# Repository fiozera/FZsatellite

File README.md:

# FZsatellite
Um satélite PocketQube Open Hardware

Projeto desenvolvido em colaboração com:

- Jonathan Querubina <https://github.com/chr0nu5>
- Pedro Kaled <https://github.com/pedrokdc>
- Edson Pavoni

Licensed under CERN-OHL-S v2 or later

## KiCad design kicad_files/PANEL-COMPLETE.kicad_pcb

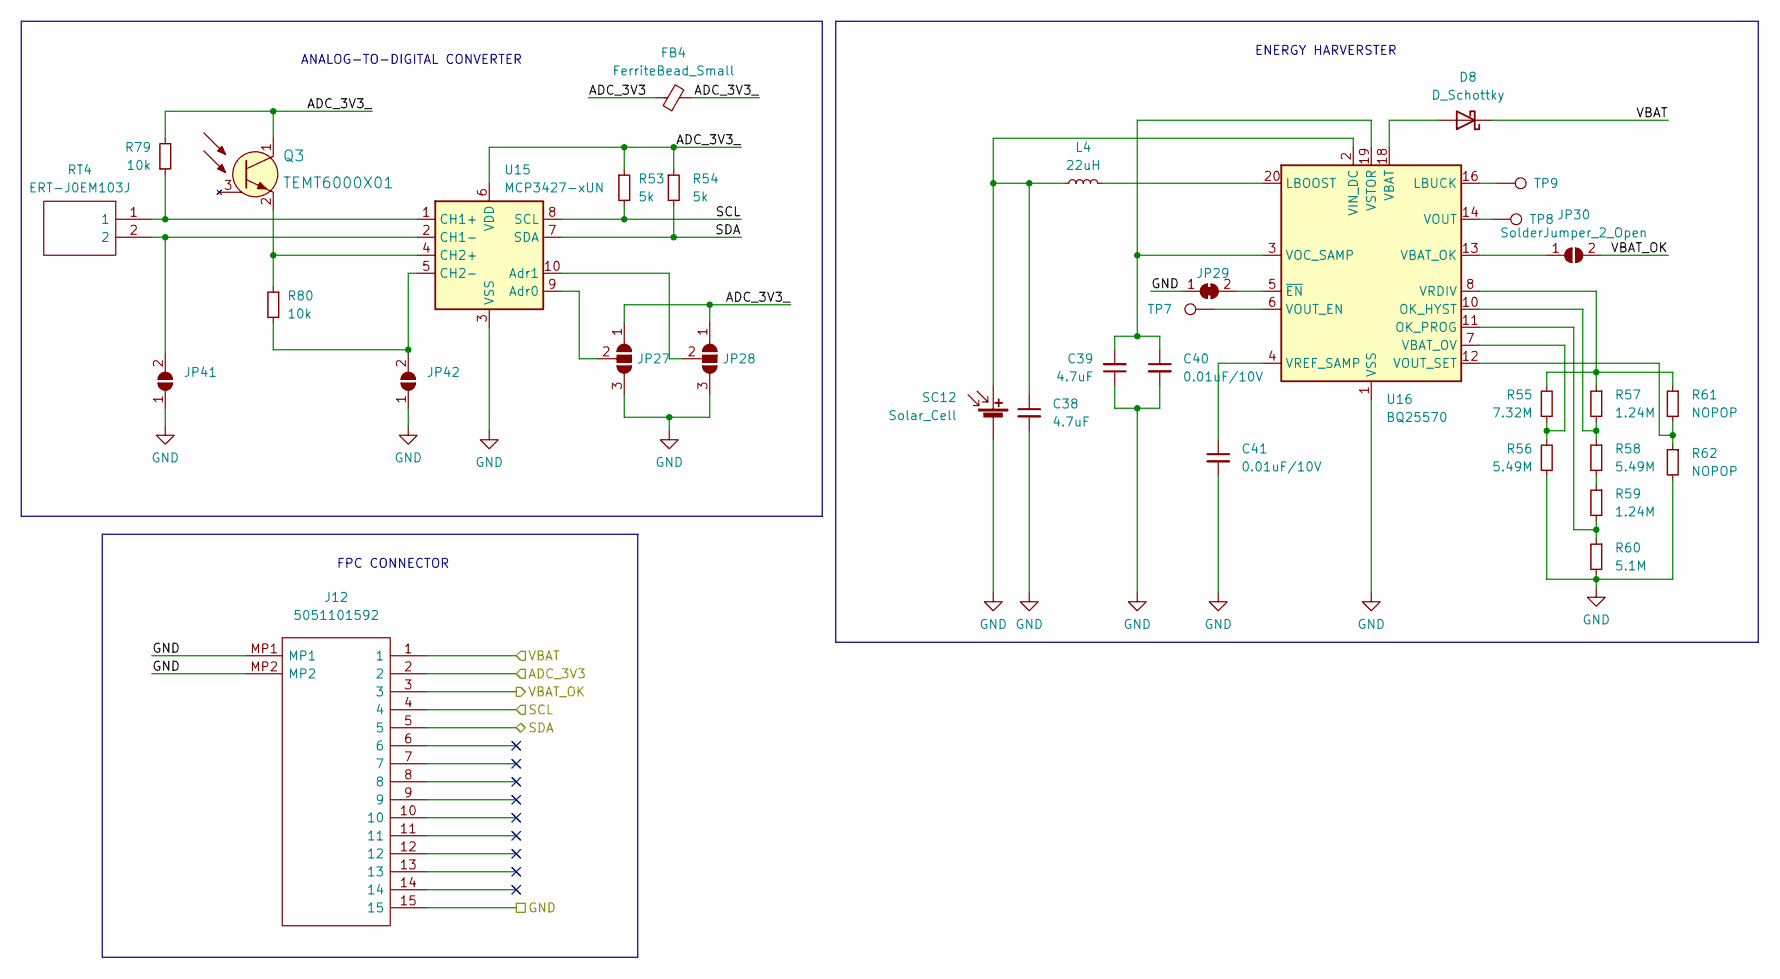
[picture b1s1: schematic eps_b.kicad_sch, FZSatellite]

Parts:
C38, C39: 4.7uF; C_0805_2012Metric
C40, C41: 0.01uF/10V; C_0402_1005Metric; Mouser Part 581-0402ZC103MAT2A
D8: D_Schottky; D_SOD-323
FB4: FerriteBead_Small; L_0603_1608Metric
J12: 5051101592; Manufacturer_Part_Number 5051101592
JP27, JP28: SolderJumper_3_Open; SolderJumper-3_P1.3mm_Open_RoundedPad1.0x1.5mm
JP29: SolderJumper_2_Bridged; SolderJumper-2_P1.3mm_Bridged_RoundedPad1.0x1.5mm
JP30, JP41, JP42: SolderJumper_2_Open; SolderJumper-2_P1.3mm_Open_RoundedPad1.0x1.5mm
L4: 22uH; LPS4018223MRC
Q3: TEMT6000X01; Phototransistor_SMD_4x2mm_TEMT6000X01; MPN TEMT6000X01; Digi-Key_PN 751-1055-1-ND
R53, R54: 5k; R_0402_1005Metric; Mouser Part 603-RC0402FR-075KL
R55: 7.32M; R_0402_1005Metric
R56, R58: 5.49M; R_0402_1005Metric
R57, R59: 1.24M; R_0402_1005Metric
R60: 5.1M; R_0402_1005Metric
R61, R62: NOPOP; R_0402_1005Metric
R79, R80: 10k; R_0603_1608Metric
RT4: ERT-J0EM103J; THRMC1005X55N; Mouser Part Number 667-ERT-J0EM103J
SC12: Solar_Cell; SM141K08LV
TP7, TP8, TP9: TestPoint; TestPoint_Pad_D1.0mm
U15: MCP3427-xUN; MSOP-10_3x3mm_P0.5mm
U16: BQ25570; QFN-20-1EP_3.5x3.5mm_P0.5mm_EP2x2mm

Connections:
/ADC_3V3: FB4.1, J12.2; also elsewhere on the board
/DEPNO: D8.1 (K), J12.1; also elsewhere on the board
/EPS B/ADC_3V3_: FB4.2, JP27.1 (A), JP28.1 (A), Q3.1 (C), R53.1, R54.1, R79.2, U15.6 (VDD)
/SCL1: J12.4, R53.2, U15.8 (SCL); also elsewhere on the board
/SDA1: J12.5, R54.2, U15.7 (SDA); also elsewhere on the board
/VBAT_OK: J12.3, JP30.2 (B); also elsewhere on the board
GND: C38.2, C39.1, C40.2, C41.2, J12.15, J12.MP1, J12.MP2, JP27.3 (B), JP28.3 (B), JP29.1 (A), JP41.1 (A), JP42.1 (A), R56.1, R60.2, R62.2, SC12.2 (-), U15.3 (VSS), U16.1 (VSS), U16.9 (VSS), U16.15 (VSS), U16.17 (VSS), U16.21 (VSS); also elsewhere on the board
unnamed: C38.1, L4.1, SC12.1 (+), U16.2 (VIN_DC)
unnamed: C39.2, C40.1, U16.3 (VOC_SAMP), U16.19 (VSTOR)
unnamed: C41.1, U16.4 (VREF_SAMP)
unnamed: D8.2 (A), U16.18 (VBAT)
unnamed: JP27.2 (C), U15.9 (Adr0)
unnamed: JP28.2 (C), U15.10 (Adr1)
unnamed: JP29.2 (B), U16.5 (~EN)
unnamed: JP30.1 (A), U16.13 (VBAT_OK)
unnamed: JP41.2 (B), RT4.2, U15.2 (CH1-)
unnamed: JP42.2 (B), R80.2, U15.5 (CH2-)
unnamed: L4.2, U16.20 (LBOOST)
unnamed: Q3.2 (E), R80.1, U15.4 (CH2+)
unnamed: R55.1, R56.2, U16.7 (VBAT_OV)
unnamed: R55.2, R57.1, R61.1, U16.8 (VRDIV)
unnamed: R57.2, R58.1, U16.10 (OK_HYST)
unnamed: R58.2, R59.1
unnamed: R59.2, R60.1, U16.11 (OK_PROG)
unnamed: R61.2, R62.1, U16.12 (VOUT_SET)
unnamed: R79.1, RT4.1, U15.1 (CH1+)
unnamed: TP7.1, U16.6 (VOUT_EN)
unnamed: TP8.1, U16.14 (VOUT)
unnamed: TP9.1, U16.16 (LBUCK)

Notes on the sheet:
FPC CONNECTOR
ANALOG-TO-DIGITAL CONVERTER
ENERGY HARVERSTER

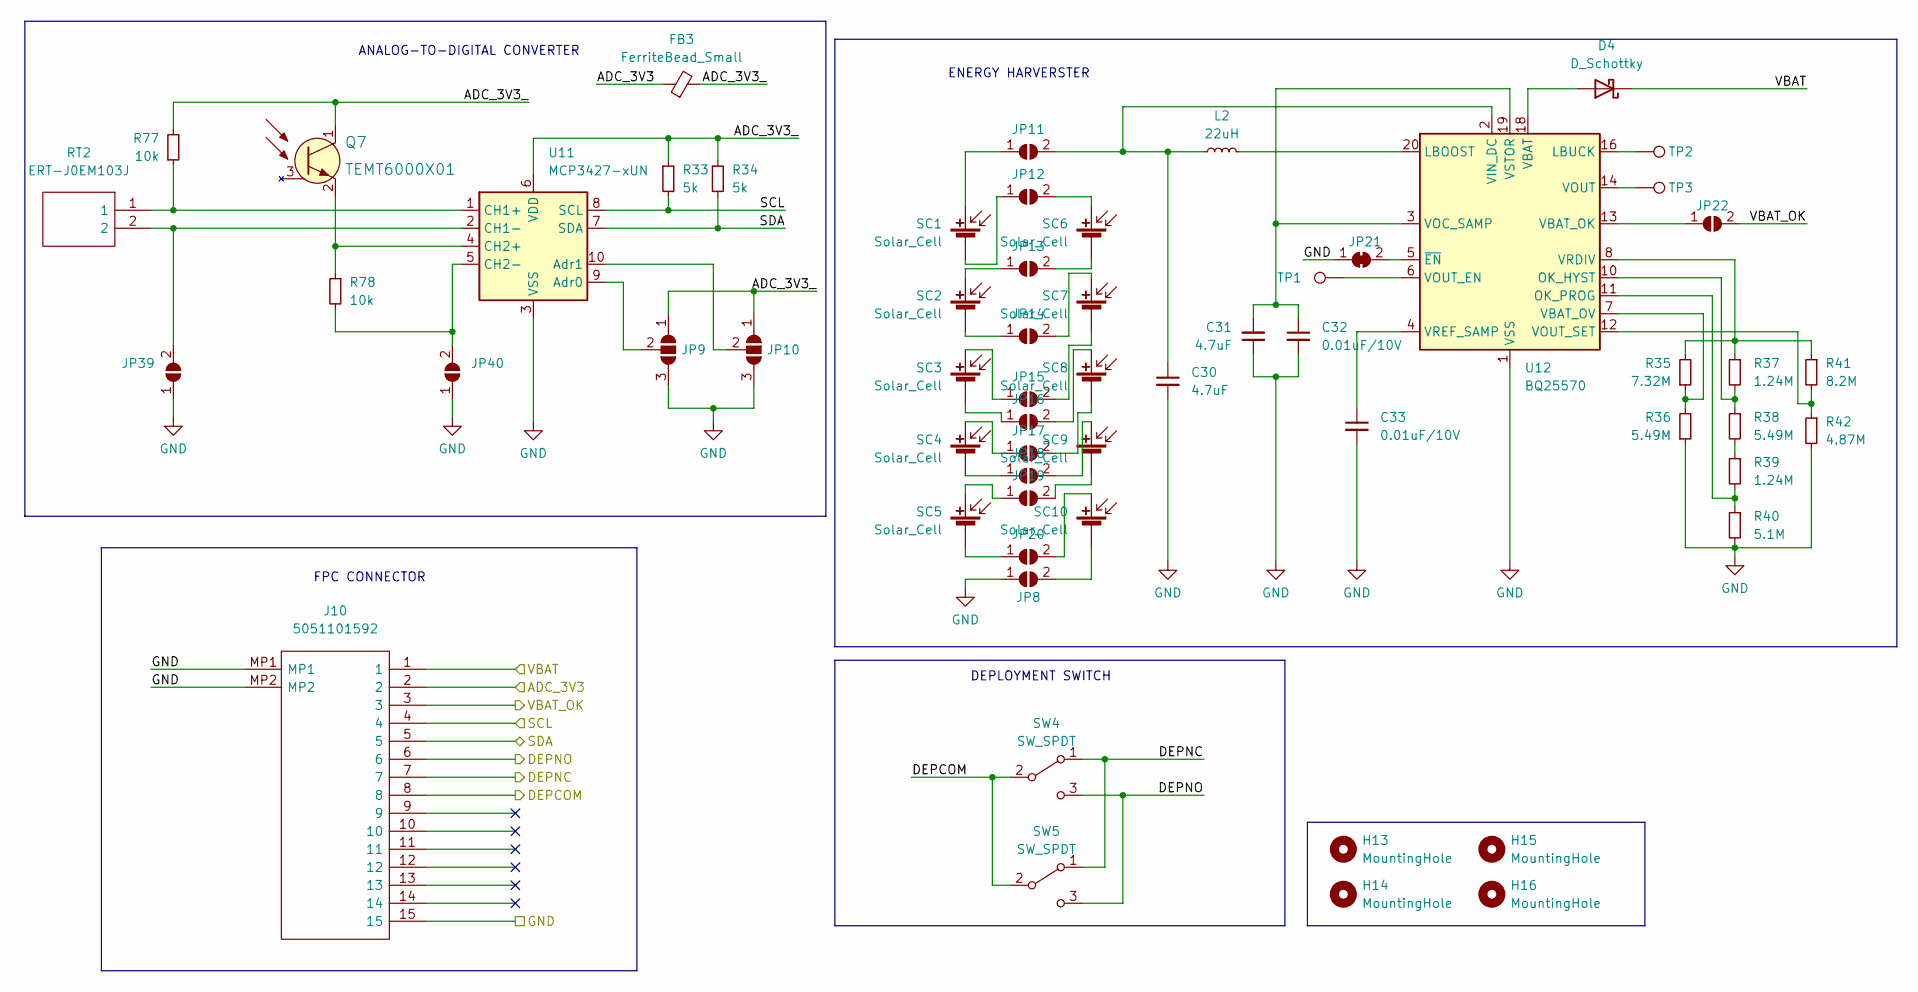
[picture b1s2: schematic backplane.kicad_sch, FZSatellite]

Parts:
C30, C31: 4.7uF; C_0805_2012Metric
C32, C33: 0.01uF/10V; C_0402_1005Metric; Mouser Part 581-0402ZC103MAT2A
D4: D_Schottky; D_SOD-323
FB3: FerriteBead_Small; L_0603_1608Metric
H13, H14, H15, H16: MountingHole; MountingHole_2.2mm_M2
J10: 5051101592; Manufacturer_Part_Number 5051101592
JP8, JP11, JP12, JP13, JP14, JP15, JP16, JP17, JP18, JP19, JP20, JP22, JP39, JP40: SolderJumper_2_Open; SolderJumper-2_P1.3mm_Open_RoundedPad1.0x1.5mm
JP9, JP10: SolderJumper_3_Open; SolderJumper-3_P1.3mm_Open_RoundedPad1.0x1.5mm
JP21: SolderJumper_2_Bridged; SolderJumper-2_P1.3mm_Bridged_RoundedPad1.0x1.5mm
L2: 22uH; LPS4018223MRC
Q7: TEMT6000X01; Phototransistor_SMD_4x2mm_TEMT6000X01; MPN TEMT6000X01; Digi-Key_PN 751-1055-1-ND
R33, R34: 5k; R_0402_1005Metric; Mouser Part 603-RC0402FR-075KL
R35: 7.32M; R_0402_1005Metric
R36, R38: 5.49M; R_0402_1005Metric
R37, R39: 1.24M; R_0402_1005Metric
R40: 5.1M; R_0402_1005Metric
R41: 8.2M; R_0402_1005Metric
R42: 4.87M; R_0402_1005Metric
R77, R78: 10k; R_0603_1608Metric
RT2: ERT-J0EM103J; THRMC1005X55N; Mouser Part Number 667-ERT-J0EM103J
SC1, SC2, SC3, SC4, SC5, SC6, SC7, SC8, SC9, SC10: Solar_Cell; KXOB25-12X1F-TR
SW4, SW5: SW_SPDT; D2F-L2-A1
TP1, TP2, TP3: TestPoint; TestPoint_Pad_D1.0mm
U11: MCP3427-xUN; MSOP-10_3x3mm_P0.5mm
U12: BQ25570; QFN-20-1EP_3.5x3.5mm_P0.5mm_EP2x2mm

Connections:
/ADC_3V3: FB3.1, J10.2; also elsewhere on the board
/BACK PLANE/ADC_3V3_: FB3.2, JP9.1 (A), JP10.1 (A), Q7.1 (C), R33.1, R34.1, R77.2, U11.6 (VDD)
/DEPCOM: J10.8, SW4.2 (B), SW5.2 (B); also elsewhere on the board
/DEPNC: J10.7, SW4.1 (A), SW5.1 (A); also elsewhere on the board
/DEPNO: D4.1 (K), J10.1, J10.6, SW4.3 (C), SW5.3 (C); also elsewhere on the board
/SCL1: J10.4, R33.2, U11.8 (SCL); also elsewhere on the board
/SDA1: J10.5, R34.2, U11.7 (SDA); also elsewhere on the board
/VBAT_OK: J10.3, JP22.2 (B); also elsewhere on the board
GND: C30.2, C31.1, C32.2, C33.2, J10.15, J10.MP1, J10.MP2, JP8.1 (A), JP9.3 (B), JP10.3 (B), JP21.1 (A), JP39.1 (A), JP40.1 (A), R36.1, R40.2, R42.2, U11.3 (VSS), U12.1 (VSS), U12.9 (VSS), U12.15 (VSS), U12.17 (VSS), U12.21 (VSS); also elsewhere on the board
unnamed: C30.1, JP11.2 (B), L2.1, U12.2 (VIN_DC)
unnamed: C31.2, C32.1, U12.3 (VOC_SAMP), U12.19 (VSTOR)
unnamed: C33.1, U12.4 (VREF_SAMP)
unnamed: D4.2 (A), U12.18 (VBAT)
unnamed: JP8.2 (B), SC10.2 (-)
unnamed: JP9.2 (C), U11.9 (Adr0)
unnamed: JP10.2 (C), U11.10 (Adr1)
unnamed: JP11.1 (A), SC1.1 (+)
unnamed: JP12.1 (A), SC1.2 (-)
unnamed: JP12.2 (B), SC6.1 (+)
unnamed: JP13.1 (A), SC2.1 (+)
unnamed: JP13.2 (B), SC6.2 (-)
unnamed: JP14.1 (A), SC2.2 (-)
unnamed: JP14.2 (B), SC7.1 (+)
unnamed: JP15.1 (A), SC3.1 (+)
unnamed: JP15.2 (B), SC7.2 (-)
unnamed: JP16.1 (A), SC3.2 (-)
unnamed: JP16.2 (B), SC8.1 (+)
unnamed: JP17.1 (A), SC4.1 (+)
unnamed: JP17.2 (B), SC8.2 (-)
unnamed: JP18.1 (A), SC4.2 (-)
unnamed: JP18.2 (B), SC9.1 (+)
unnamed: JP19.1 (A), SC5.1 (+)
unnamed: JP19.2 (B), SC9.2 (-)
unnamed: JP20.1 (A), SC5.2 (-)
unnamed: JP20.2 (B), SC10.1 (+)
unnamed: JP21.2 (B), U12.5 (~EN)
unnamed: JP22.1 (A), U12.13 (VBAT_OK)
unnamed: JP39.2 (B), RT2.2, U11.2 (CH1-)
unnamed: JP40.2 (B), R78.2, U11.5 (CH2-)
unnamed: L2.2, U12.20 (LBOOST)
unnamed: Q7.2 (E), R78.1, U11.4 (CH2+)
unnamed: R35.1, R36.2, U12.7 (VBAT_OV)
unnamed: R35.2, R37.1, R41.1, U12.8 (VRDIV)
unnamed: R37.2, R38.1, U12.10 (OK_HYST)
unnamed: R38.2, R39.1
unnamed: R39.2, R40.1, U12.11 (OK_PROG)
unnamed: R41.2, R42.1, U12.12 (VOUT_SET)
unnamed: R77.1, RT2.1, U11.1 (CH1+)
unnamed: TP1.1, U12.6 (VOUT_EN)
unnamed: TP2.1, U12.16 (LBUCK)
unnamed: TP3.1, U12.14 (VOUT)

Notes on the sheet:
DEPLOYMENT SWITCH
ANALOG-TO-DIGITAL CONVERTER
FPC CONNECTOR
ENERGY HARVERSTER

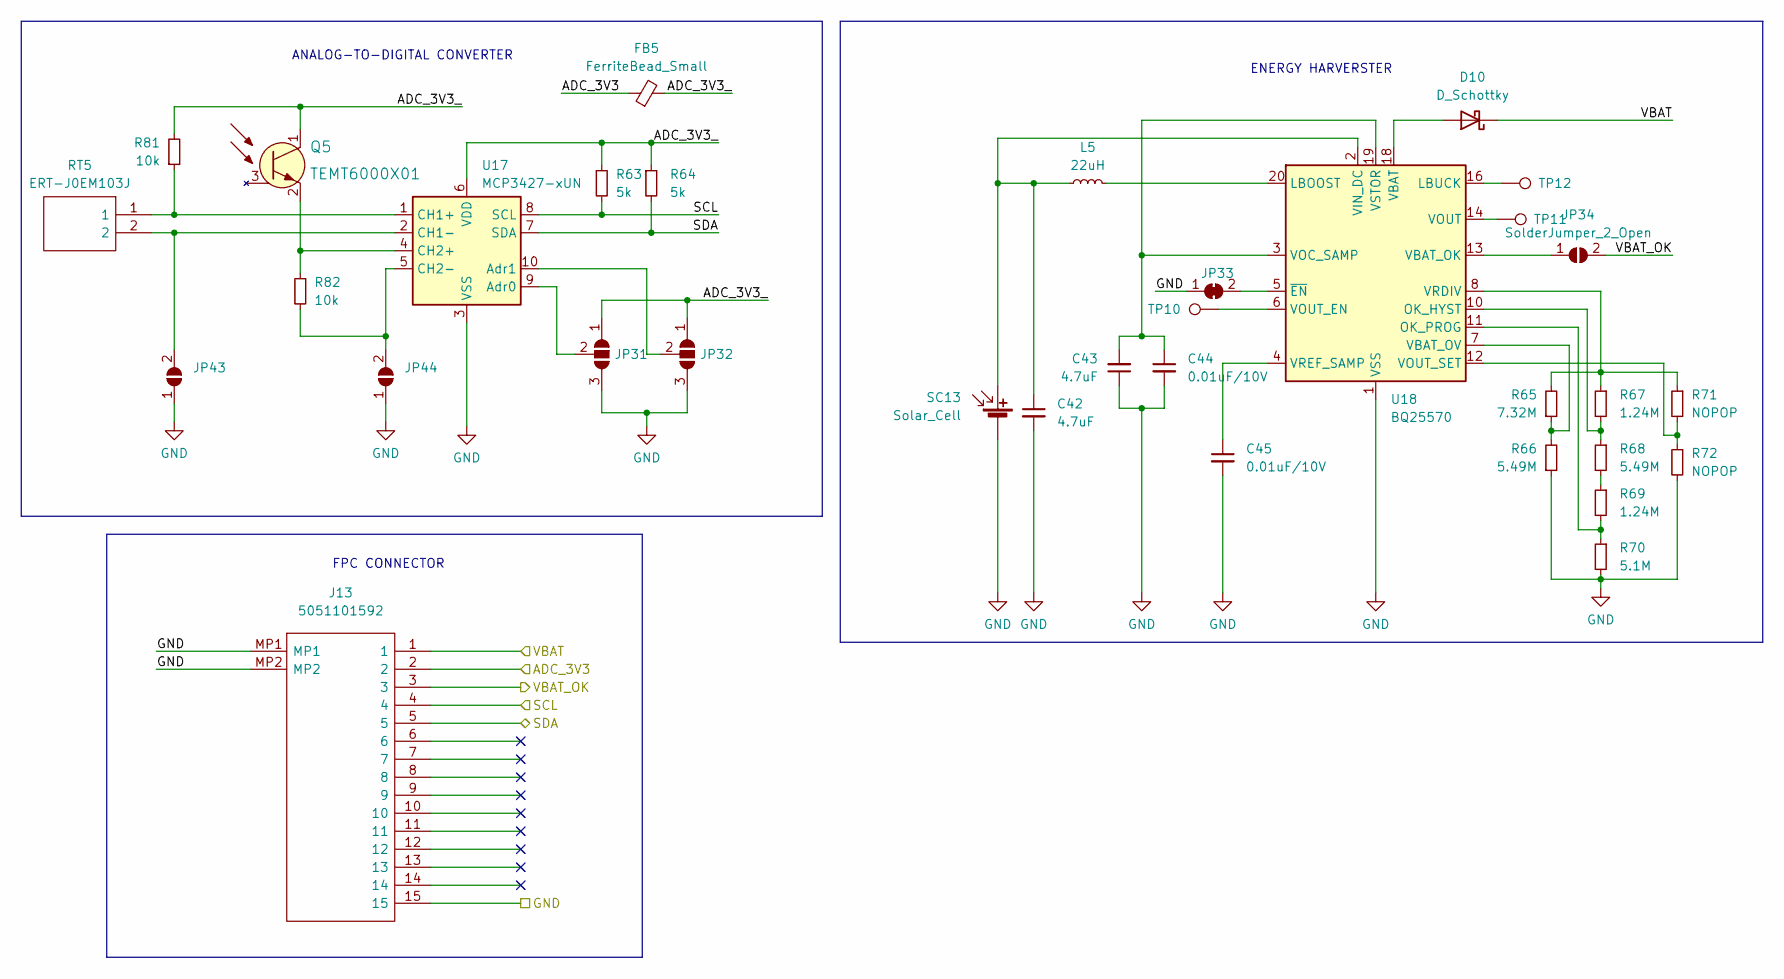
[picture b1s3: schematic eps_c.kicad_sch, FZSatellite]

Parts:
C42, C43: 4.7uF; C_0805_2012Metric
C44, C45: 0.01uF/10V; C_0402_1005Metric; Mouser Part 581-0402ZC103MAT2A
D10: D_Schottky; D_SOD-323
FB5: FerriteBead_Small; L_0603_1608Metric
J13: 5051101592; Manufacturer_Part_Number 5051101592
JP31, JP32: SolderJumper_3_Open; SolderJumper-3_P1.3mm_Open_RoundedPad1.0x1.5mm
JP33: SolderJumper_2_Bridged; SolderJumper-2_P1.3mm_Bridged_RoundedPad1.0x1.5mm
JP34, JP43, JP44: SolderJumper_2_Open; SolderJumper-2_P1.3mm_Open_RoundedPad1.0x1.5mm
L5: 22uH; LPS4018223MRC
Q5: TEMT6000X01; Phototransistor_SMD_4x2mm_TEMT6000X01; MPN TEMT6000X01; Digi-Key_PN 751-1055-1-ND
R63, R64: 5k; R_0402_1005Metric; Mouser Part 603-RC0402FR-075KL
R65: 7.32M; R_0402_1005Metric
R66, R68: 5.49M; R_0402_1005Metric
R67, R69: 1.24M; R_0402_1005Metric
R70: 5.1M; R_0402_1005Metric
R71, R72: NOPOP; R_0402_1005Metric
R81, R82: 10k; R_0603_1608Metric
RT5: ERT-J0EM103J; THRMC1005X55N; Mouser Part Number 667-ERT-J0EM103J
SC13: Solar_Cell; SM141K08LV
TP10, TP11, TP12: TestPoint; TestPoint_Pad_D1.0mm
U17: MCP3427-xUN; MSOP-10_3x3mm_P0.5mm
U18: BQ25570; QFN-20-1EP_3.5x3.5mm_P0.5mm_EP2x2mm

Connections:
/ADC_3V3: FB5.1, J13.2; also elsewhere on the board
/DEPNO: D10.1 (K), J13.1; also elsewhere on the board
/EPS C/ADC_3V3_: FB5.2, JP31.1 (A), JP32.1 (A), Q5.1 (C), R63.1, R64.1, R81.2, U17.6 (VDD)
/SCL1: J13.4, R63.2, U17.8 (SCL); also elsewhere on the board
/SDA1: J13.5, R64.2, U17.7 (SDA); also elsewhere on the board
/VBAT_OK: J13.3, JP34.2 (B); also elsewhere on the board
GND: C42.2, C43.1, C44.2, C45.2, J13.15, J13.MP1, J13.MP2, JP31.3 (B), JP32.3 (B), JP33.1 (A), JP43.1 (A), JP44.1 (A), R66.1, R70.2, R72.2, SC13.2 (-), U17.3 (VSS), U18.1 (VSS), U18.9 (VSS), U18.15 (VSS), U18.17 (VSS), U18.21 (VSS); also elsewhere on the board
unnamed: C42.1, L5.1, SC13.1 (+), U18.2 (VIN_DC)
unnamed: C43.2, C44.1, U18.3 (VOC_SAMP), U18.19 (VSTOR)
unnamed: C45.1, U18.4 (VREF_SAMP)
unnamed: D10.2 (A), U18.18 (VBAT)
unnamed: JP31.2 (C), U17.9 (Adr0)
unnamed: JP32.2 (C), U17.10 (Adr1)
unnamed: JP33.2 (B), U18.5 (~EN)
unnamed: JP34.1 (A), U18.13 (VBAT_OK)
unnamed: JP43.2 (B), RT5.2, U17.2 (CH1-)
unnamed: JP44.2 (B), R82.2, U17.5 (CH2-)
unnamed: L5.2, U18.20 (LBOOST)
unnamed: Q5.2 (E), R82.1, U17.4 (CH2+)
unnamed: R65.1, R66.2, U18.7 (VBAT_OV)
unnamed: R65.2, R67.1, R71.1, U18.8 (VRDIV)
unnamed: R67.2, R68.1, U18.10 (OK_HYST)
unnamed: R68.2, R69.1
unnamed: R69.2, R70.1, U18.11 (OK_PROG)
unnamed: R71.2, R72.1, U18.12 (VOUT_SET)
unnamed: R81.1, RT5.1, U17.1 (CH1+)
unnamed: TP10.1, U18.6 (VOUT_EN)
unnamed: TP11.1, U18.14 (VOUT)
unnamed: TP12.1, U18.16 (LBUCK)

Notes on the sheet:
ANALOG-TO-DIGITAL CONVERTER
FPC CONNECTOR
ENERGY HARVERSTER

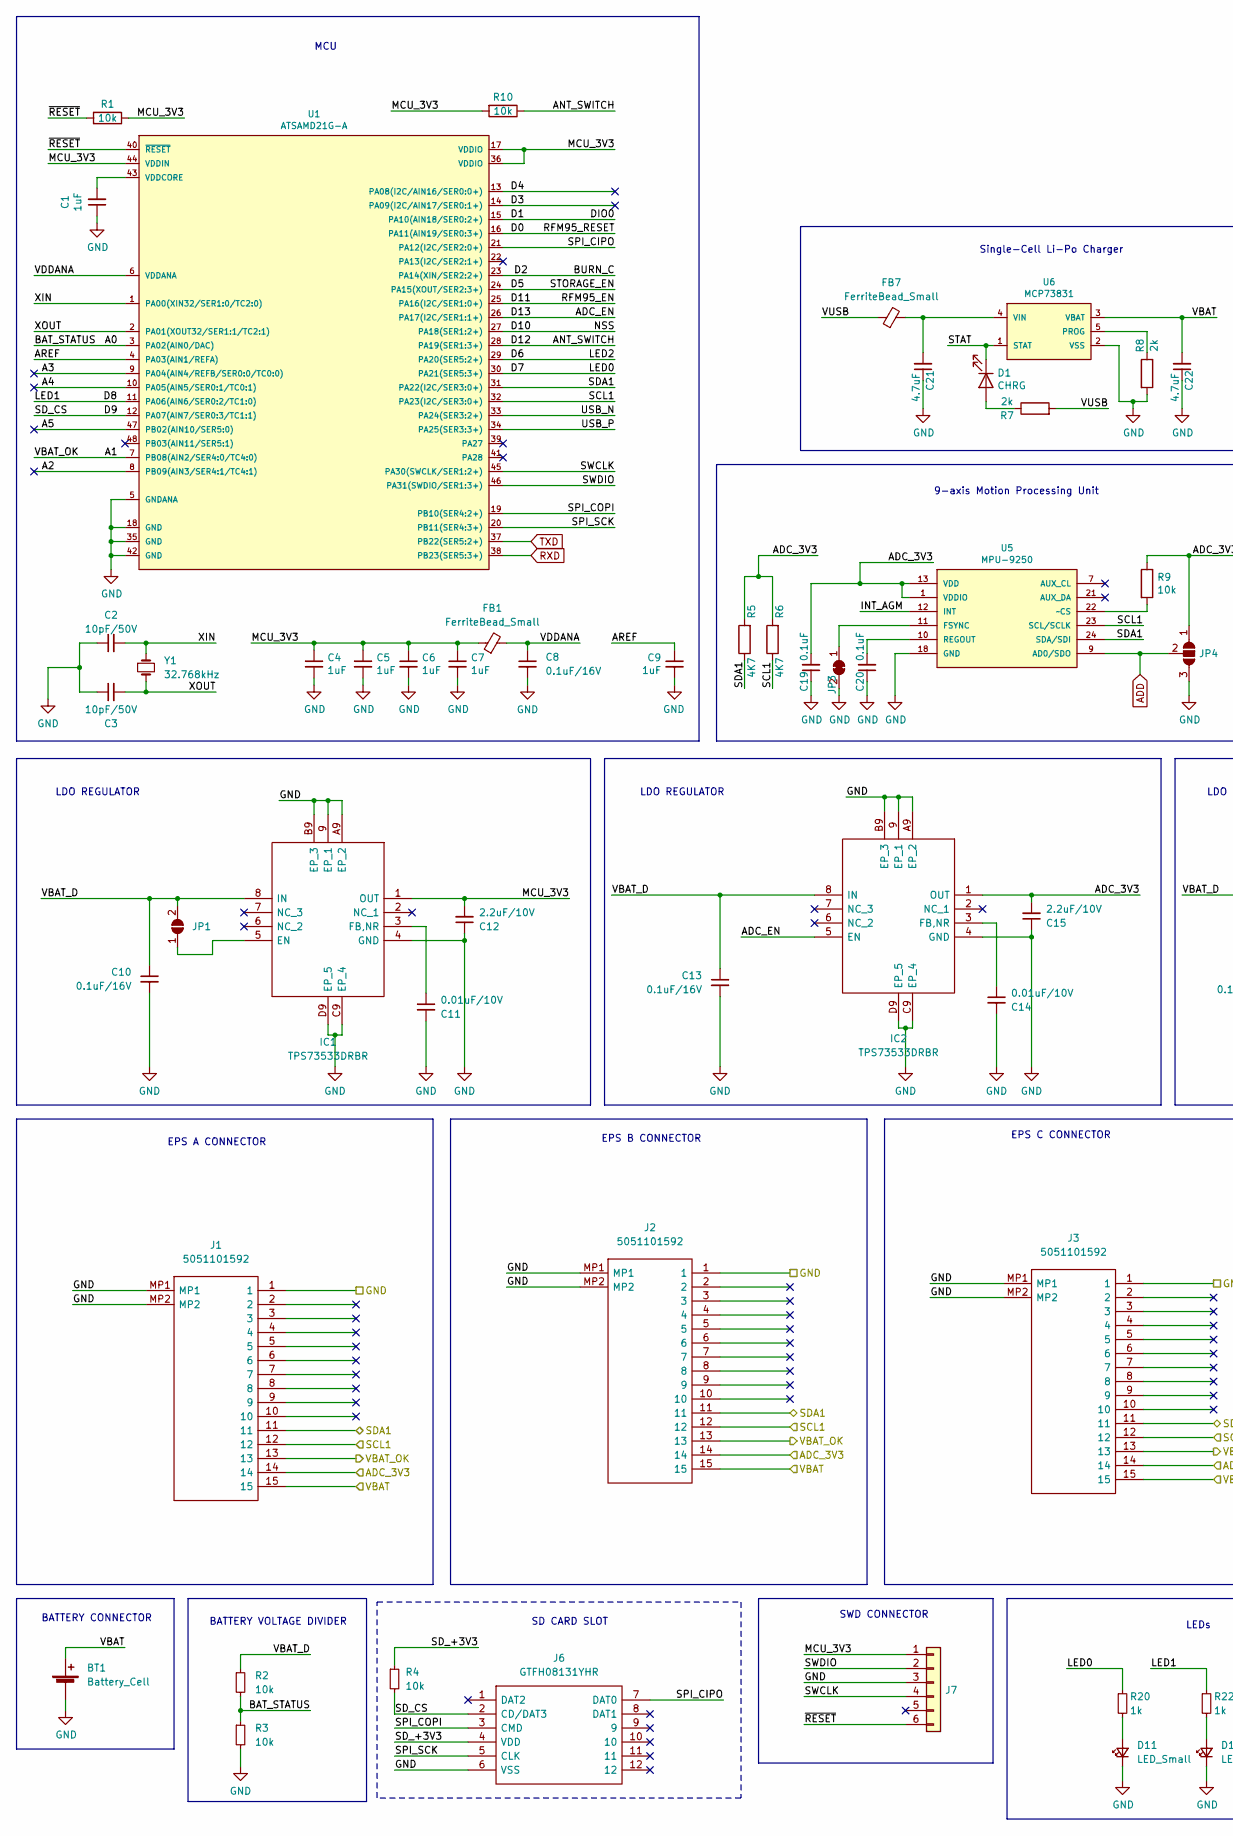
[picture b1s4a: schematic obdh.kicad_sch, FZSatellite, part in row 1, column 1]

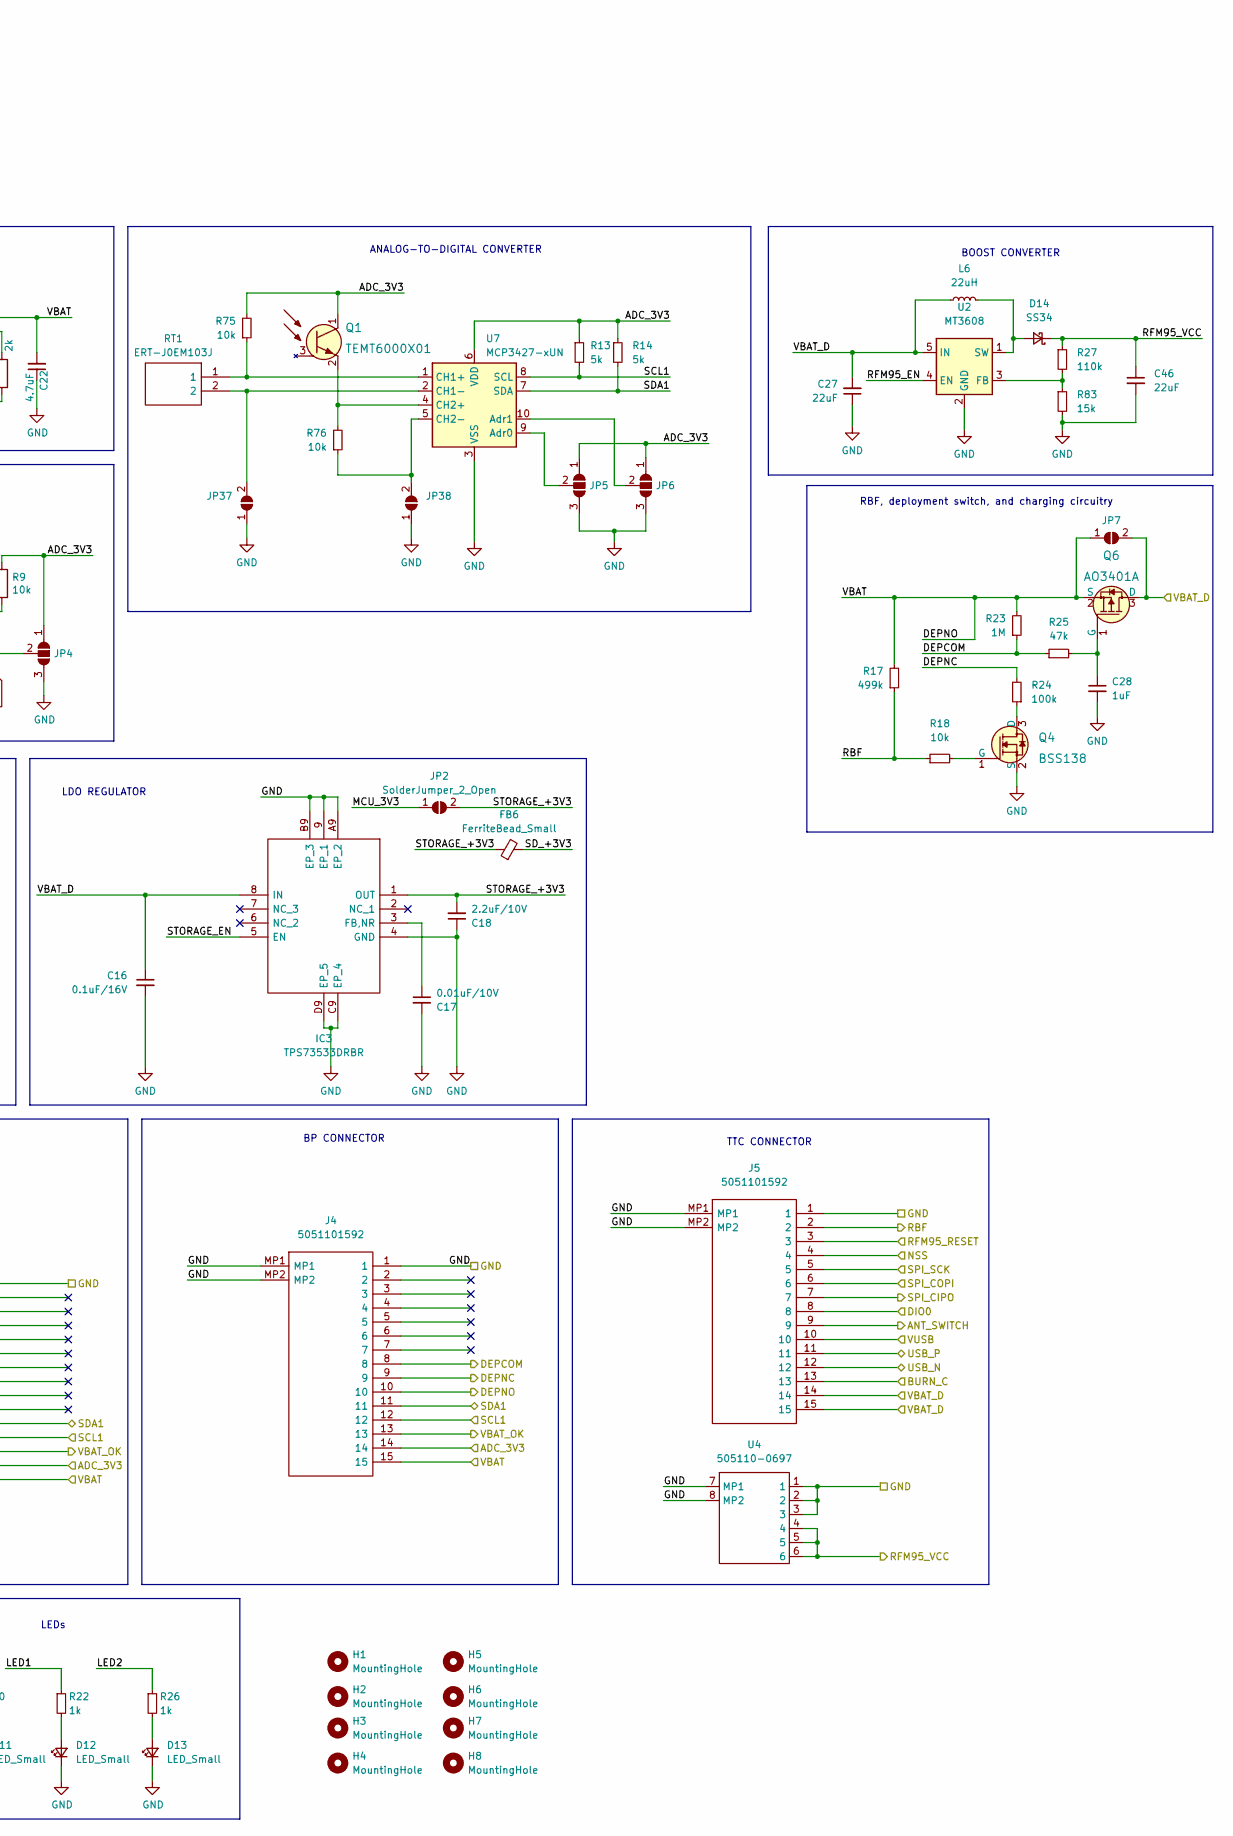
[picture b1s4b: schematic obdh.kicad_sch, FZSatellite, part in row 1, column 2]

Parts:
BT1: Battery_Cell; JST_PH_B2B-PH-K_1x02_P2.00mm_Vertical
C1, C4, C5, C6, C7, C9, C28: 1uF; C_0603_1608Metric
C2, C3: 10pF/50V; C_0402_1005Metric; Mouser Part 81-GCM1555C1H100JA6D
C8, C10, C13, C16: 0.1uF/16V; C_0402_1005Metric; Mouser Part 81-GCM155R71C104KA5D
C11, C14, C17: 0.01uF/10V; C_0402_1005Metric; Mouser Part 581-0402ZC103MAT2A
C12, C15, C18: 2.2uF/10V; C_0603_1608Metric; Mouser Part 81-GRM188R71A225KE15
C19, C20: 0.1uF; C_0603_1608Metric
C21, C22: 4.7uF; C_0603_1608Metric
C27, C46: 22uF; C_1206_3216Metric
D1: CHRG; LED_0603_1608Metric
D11, D12, D13: LED_Small; LED_0603_1608Metric
D14: SS34; D_SMA
FB1, FB6, FB7: FerriteBead_Small; L_0603_1608Metric
H1, H2, H3, H4, H5, H6, H7, H8: MountingHole; MountingHole_2.2mm_M2
IC1, IC2, IC3: TPS73533DRBR; Mouser Part Number 595-TPS73533DRBR
J1, J2, J3, J4, J5: 5051101592; Manufacturer_Part_Number 5051101592
J6: GTFH08131YHR; Mouser Part Number 523-GTFH08131YHR
J7: Conn_01x06; Tag-Connect_TC2030-IDC-NL_2x03_P1.27mm_Vertical
JP1, JP2, JP7, JP37, JP38: SolderJumper_2_Open; SolderJumper-2_P1.3mm_Open_RoundedPad1.0x1.5mm
JP3: SolderJumper_2_Bridged; SolderJumper-2_P1.3mm_Bridged_RoundedPad1.0x1.5mm
JP4, JP5, JP6: SolderJumper_3_Open; SolderJumper-3_P1.3mm_Open_RoundedPad1.0x1.5mm
L6: 22uH; L_6.3x6.3_H3
Q1: TEMT6000X01; Phototransistor_SMD_4x2mm_TEMT6000X01; MPN TEMT6000X01; Digi-Key_PN 751-1055-1-ND
Q4: BSS138; SOT-23-3; MPN BSS138; Digi-Key_PN BSS138CT-ND
Q6: AO3401A; SOT-23-3; MPN AO3401A; Digi-Key_PN 785-1001-1-ND
R1, R2, R3, R9, R10, R18, R75, R76: 10k; R_0603_1608Metric
R4: 10k; R_0402_1005Metric; Mouser Part 603-RC0402FR-1010KL
R5, R6: 4K7; R_0603_1608Metric
R7, R8: 2k; R_0603_1608Metric
R13, R14: 5k; R_0402_1005Metric; Mouser Part 603-RC0402FR-075KL
R17: 499k; R_0603_1608Metric
R20, R22, R26: 1k; R_0603_1608Metric
R23: 1M; R_0603_1608Metric
R24: 100k; R_0603_1608Metric
R25: 47k; R_0603_1608Metric
R27: 110k; R_0603_1608Metric
R83: 15k; R_0603_1608Metric
RT1: ERT-J0EM103J; THRMC1005X55N; Mouser Part Number 667-ERT-J0EM103J
U1: ATSAMD21G-A; TQFP-48_7x7mm_P0.5mm
U2: MT3608; SOT-23-6
U4: 505110-0697; 5051100692
U5: MPU-9250; QFN-24-1EP_3x3mm_P0.4mm_EP1.75x1.6mm
U6: MCP73831; SOT23-5
U7: MCP3427-xUN; MSOP-10_3x3mm_P0.5mm
Y1: 32.768kHz; Crystal_SMD_2012-2Pin_2.0x1.2mm; Mouser Part 710-830062558

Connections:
/ADC_3V3: C15.2, C19.2, IC2.1 (OUT), J1.14, J2.14, J3.14, J4.14, JP4.1 (A), JP5.1 (A), JP6.1 (A), Q1.1 (C), R5.2, R6.2, R9.1, R13.1, R14.1, R75.2, U5.1 (VDDIO), U5.8 (VDDIO), U5.13 (VDD), U7.6 (VDD); also elsewhere on the board
/ANT_SWITCH: J5.9, R10.1, U1.28 (PA19(SER1:3+)); also elsewhere on the board
/BURN_C: J5.13, U1.23 (PA14(XIN/SER2:2+)); also elsewhere on the board
/DEPCOM: J4.8, R23.1, R25.1; also elsewhere on the board
/DEPNC: J4.9, R24.2; also elsewhere on the board
/DEPNO: BT1.1 (+), C22.2, J1.15, J2.15, J3.15, J4.10, J4.15, JP7.1 (A), Q6.2 (S), R17.2, R23.2, U6.3 (VBAT); also elsewhere on the board
/DIO0: J5.8, U1.15 (PA10(AIN18/SER0:2+)); also elsewhere on the board
/NSS: J5.4, U1.27 (PA18(SER1:2+)); also elsewhere on the board
/OBDH/A0: R2.2, R3.1, U1.3 (PA02(AIN0/DAC))
/OBDH/A2: U1.8 (PB09(AIN3/SER4:1/TC4:1))
/OBDH/A3: U1.9 (PA04(AIN4/REFB/SER0:0/TC0:0))
/OBDH/A4: U1.10 (PA05(AIN5/SER0:1/TC0:1))
/OBDH/A5: U1.47 (PB02(AIN10/SER5:0))
/OBDH/ADC_EN: IC2.5 (EN), U1.26 (PA17(I2C/SER1:1+))
/OBDH/AREF: C9.1, U1.4 (PA03(AIN1/REFA))
/OBDH/D3: U1.14 (PA09(I2C/AIN17/SER0:1+))
/OBDH/D4: U1.13 (PA08(I2C/AIN16/SER0:0+))
/OBDH/D5: IC3.5 (EN), U1.24 (PA15(XOUT/SER2:3+))
/OBDH/D6: R26.1, U1.29 (PA20(SER5:2+))
/OBDH/D7: R20.1, U1.30 (PA21(SER5:3+))
/OBDH/D8: R22.1, U1.11 (PA06(AIN6/SER0:2/TC1:0))
/OBDH/D9: J6.2 (CD/DAT3), R4.2, U1.12 (PA07(AIN7/SER0:3/TC1:1))
/OBDH/D11: U1.25 (PA16(I2C/SER1:0+)), U2.4 (EN)
/OBDH/INT_AGM: U5.12 (INT)
/OBDH/MCU_3V3: C4.1, C5.1, C6.1, C7.1, C12.2, FB1.1, IC1.1 (OUT), J7.1, JP2.1 (A), R1.1, R10.2, U1.17 (VDDIO), U1.36 (VDDIO), U1.44 (VDDIN)
/OBDH/SD_+3V3: FB6.2, J6.4 (VDD), R4.1
/OBDH/STAT: D1.1 (K), U6.1 (STAT)
/OBDH/STORAGE_+3V3: C18.2, FB6.1, IC3.1 (OUT), JP2.2 (B)
/OBDH/SWCLK: J7.4, U1.45 (PA30(SWCLK/SER1:2+))
/OBDH/SWDIO: J7.2, U1.46 (PA31(SWDIO/SER1:3+))
/OBDH/VDDANA: C8.1, FB1.2, U1.6 (VDDANA)
/OBDH/XIN: C2.2, U1.1 (PA00(XIN32/SER1:0/TC2:0)), Y1.1
/OBDH/XOUT: C3.2, U1.2 (PA01(XOUT32/SER1:1/TC2:1)), Y1.2
/OBDH/~RESET: J7.6, R1.2, U1.40 (~RESET)
/RBF: J5.2, R17.1, R18.1; also elsewhere on the board
/RFM95_RESET: J5.3, U1.16 (PA11(AIN19/SER0:3+)); also elsewhere on the board
/RFM95_VCC: C46.1, D14.1 (K), R27.1, U4.4, U4.5, U4.6; also elsewhere on the board
/SCL1: J1.12, J2.12, J3.12, J4.12, R6.1, R13.2, U1.32 (PA23(I2C/SER3:0+)), U5.23 (SCL/SCLK), U7.8 (SCL); also elsewhere on the board
/SDA1: J1.11, J2.11, J3.11, J4.11, R5.1, R14.2, U1.31 (PA22(I2C/SER3:0+)), U5.24 (SDA/SDI), U7.7 (SDA); also elsewhere on the board
/SPI_CIPO: J5.7, J6.7 (DAT0), U1.21 (PA12(I2C/SER2:0+)); also elsewhere on the board
/SPI_COPI: J5.6, J6.3 (CMD), U1.19 (PB10(SER4:2+)); also elsewhere on the board
/SPI_SCK: J5.5, J6.5 (CLK), U1.20 (PB11(SER4:3+)); also elsewhere on the board
/USB_N: J5.12, U1.33 (PA24(SER3:2+)); also elsewhere on the board
/USB_P: J5.11, U1.34 (PA25(SER3:3+)); also elsewhere on the board
/VBAT_D: C10.1, C13.1, C16.1, C27.2, IC1.8 (IN), IC2.8 (IN), IC3.8 (IN), J5.14, J5.15, JP1.2 (B), JP7.2 (B), L6.1, Q6.3 (D), R2.1, U2.5 (IN); also elsewhere on the board
/VBAT_OK: J1.13, J2.13, J3.13, J4.13, U1.7 (PB08(AIN2/SER4:0/TC4:0)); also elsewhere on the board
/VUSB: FB7.1, J5.10, R7.2; also elsewhere on the board
ADD: JP4.2 (C), U5.9 (AD0/SDO)
GND: BT1.2 (-), C1.1, C2.1, C3.1, C4.2, C5.2, C6.2, C7.2, C8.2, C9.2, C10.2, C11.2, C12.1, C13.2, C14.2, C15.1, C16.2, C17.2, C18.1, C19.1, C20.1, C21.1, C22.1, C27.1, C28.2, C46.2, D11.1 (K), D12.1 (K), D13.1 (K), IC1.4 (GND), IC1.9 (EP_1), IC1.A9 (EP_2), IC1.B9 (EP_3), IC1.C9 (EP_4), IC1.D9 (EP_5), IC2.4 (GND), IC2.9 (EP_1), IC2.A9 (EP_2), IC2.B9 (EP_3), IC2.C9 (EP_4), IC2.D9 (EP_5), IC3.4 (GND), IC3.9 (EP_1), IC3.A9 (EP_2), IC3.B9 (EP_3), IC3.C9 (EP_4), IC3.D9 (EP_5), J1.1, J1.MP1, J1.MP2, J2.1, J2.MP1, J2.MP2, J3.1, J3.MP1, J3.MP2, J4.1, J4.MP1, J4.MP2, J5.1, J5.MP1, J5.MP2, J6.6 (VSS), J7.3, JP3.2 (B), JP4.3 (B), JP5.3 (B), JP6.3 (B), JP37.1 (A), JP38.1 (A), Q4.2 (S), R3.2, R8.2, R83.2, U1.5 (GNDANA), U1.18 (GND), U1.35 (GND), U1.42 (GND), U2.2 (GND), U4.1, U4.2, U4.3, U4.7 (MP1), U4.8 (MP2), U5.18 (GND), U5.20 (GND), U6.2 (VSS), U7.3 (VSS); also elsewhere on the board
unnamed: C1.2, U1.43 (VDDCORE)
unnamed: C11.1, IC1.3 (FB,NR)
unnamed: C14.1, IC2.3 (FB,NR)
unnamed: C17.1, IC3.3 (FB,NR)
unnamed: C20.2, U5.10 (REGOUT)
unnamed: C21.2, FB7.2, U6.4 (VIN)
unnamed: C28.1, Q6.1 (G), R25.2
unnamed: D1.2 (A), R7.1
unnamed: D11.2 (A), R20.2
unnamed: D12.2 (A), R22.2
unnamed: D13.2 (A), R26.2
unnamed: D14.2 (A), L6.2, U2.1 (SW)
unnamed: IC1.5 (EN), JP1.1 (A)
unnamed: JP3.1 (A), U5.11 (FSYNC)
unnamed: JP5.2 (C), U7.9 (Adr0)
unnamed: JP6.2 (C), U7.10 (Adr1)
unnamed: JP37.2 (B), RT1.2, U7.2 (CH1-)
unnamed: JP38.2 (B), R76.1, U7.5 (CH2-)
unnamed: Q1.2 (E), R76.2, U7.4 (CH2+)
unnamed: Q4.1 (G), R18.2
unnamed: Q4.3 (D), R24.1
unnamed: R8.1, U6.5 (PROG)
unnamed: R9.2, U5.22 (~CS)
unnamed: R27.2, R83.1, U2.3 (FB)
unnamed: R75.1, RT1.1, U7.1 (CH1+)
RXD: U1.38 (PB23(SER5:3+))
TXD: U1.37 (PB22(SER5:2+))

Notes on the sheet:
LEDs
BATTERY CONNECTOR
RBF, deployment switch, and charging circuitry
BATTERY VOLTAGE DIVIDER
EPS B CONNECTOR
SD CARD SLOT
MCU
9-axis Motion Processing Unit
TTC CONNECTOR
SWD CONNECTOR
BOOST CONVERTER
ANALOG-TO-DIGITAL CONVERTER
Single-Cell Li-Po Charger
LDO REGULATOR
BP CONNECTOR
EPS A CONNECTOR
EPS C CONNECTOR
